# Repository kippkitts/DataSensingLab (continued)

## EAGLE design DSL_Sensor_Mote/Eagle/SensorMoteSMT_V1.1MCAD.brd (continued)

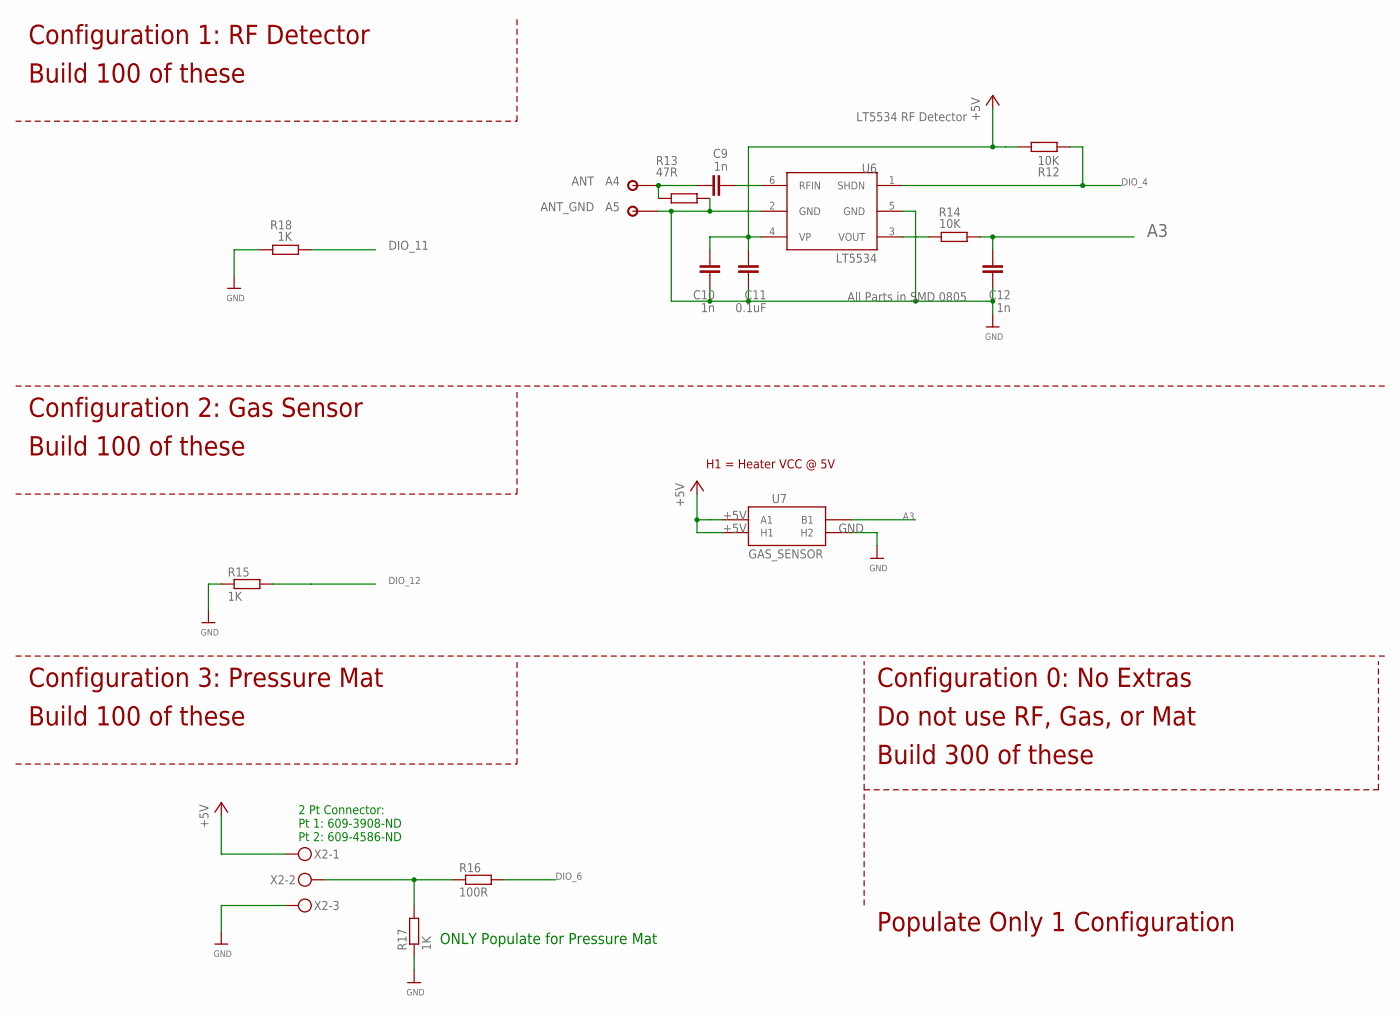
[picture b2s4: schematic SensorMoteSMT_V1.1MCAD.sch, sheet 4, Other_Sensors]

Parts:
A4: ANT; PAD146
A5: ANT_GND; PAD146
C9, C10, C12: 1n; C0805K
C11: 0.1uF; C0805K
R12, R14: 10K; R0805
R13: 47R; R0805
R15, R17, R18: 1K; R0805
R16: 100R; R0805
U6: LT5534; SC70
U7: GAS_SENSOR; MQ-3
X2: MKDSN1,5/3-5,08

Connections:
+5V: C10.2, C11.2, R12.2, U6.4 (VP), U7.A1, U7.HA (H1), X2.1; also elsewhere on the board
A3: C12.2, R14.2, U7.B1; also elsewhere on the board
DIO_4: R12.1, U6.1 (SHDN); also elsewhere on the board
DIO_6: R16.2; also elsewhere on the board
DIO_11: R18.2; also elsewhere on the board
DIO_12: R15.2; also elsewhere on the board
GND: A5.1, C10.1, C11.1, C12.1, R13.2, R15.1, R17.1, R18.1, U6.2 (GND), U6.5 (GND), U7.HB (H2), X2.3; also elsewhere on the board
unnamed: C9.1, U6.6 (RFIN)
unnamed: A4.1, C9.2, R13.1
unnamed: R14.1, U6.3 (VOUT)
unnamed: R16.1, R17.2, X2.2

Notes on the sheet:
All Parts in SMD 0805
LT5534 RF Detector
H1 = Heater VCC @ 5V
ONLY Populate for Pressure Mat
2 Pt Connector: Pt 1: 609-3908-ND Pt 2: 609-4586-ND
Configuration 3: Pressure Mat
Configuration 0: No Extras
Build 100 of these
Build 300 of these
Do not use RF, Gas, or Mat
Configuration 2: Gas Sensor
Configuration 1: RF Detector
Populate Only 1 Configuration

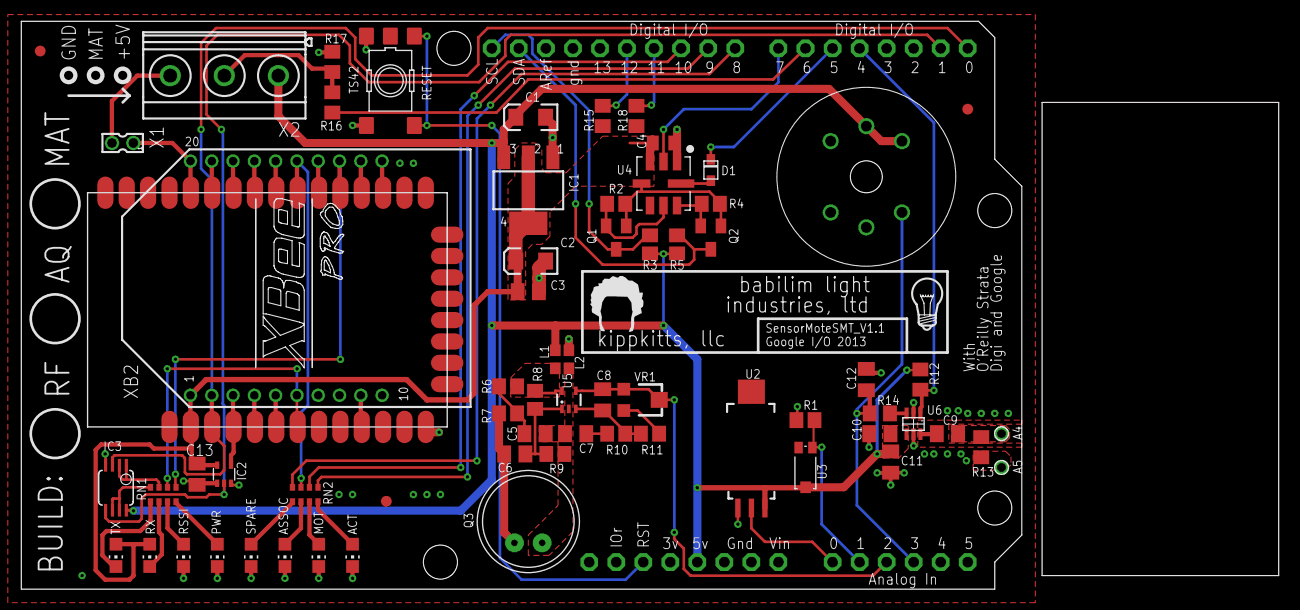
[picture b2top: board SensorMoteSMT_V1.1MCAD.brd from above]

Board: 2 copper layers, 118.1 x 53.3 mm, 70 parts (0 on the bottom side), 61 nets.

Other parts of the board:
U$5: TOP_DOCU_5MM
U$7: BABILIM_7.5MM

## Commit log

2013-09-24 First Edit
    This is the first version of the DSL Workshop Shield code.
2014-02-20 reorganized folders
2014-02-28 Added kippkitts testing program
    This is the starting point for programs that run on the sensor motes
2014-02-28 Added new version of DSL Arduino code, which allows the sensor mote to interface with a Processing based graphical user interface.
2014-02-28 Processing Visualization
2014-03-10 Reorganize Folders
2014-03-26 Moved Google IO 2013 files into DSL
2014-08-04 ONA Sensor Mote Project
    Files for the MSP430 + XBee sensor mote
2014-12-17 Removed and Replaced Bad Arduino Code
2014-12-17 Added Adafruit BMP085 Library Links
2015-03-27 Datasheet uploads
2015-03-29 Added Schematic PDFs, Fixed Code
    Added Eagle PDFs for all configurations, deleted broken Arduino code,
    added basic Arduino test program
